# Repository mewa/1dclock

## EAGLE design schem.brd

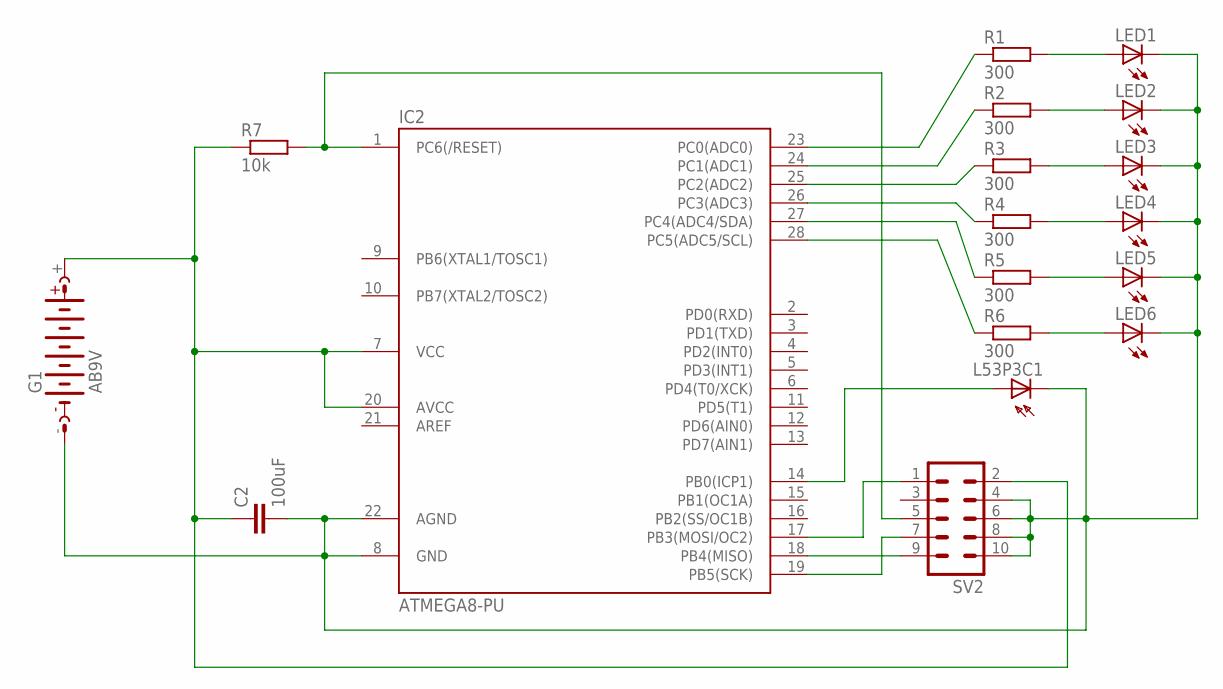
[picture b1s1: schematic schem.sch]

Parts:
C2: 100uF; C025-050X050
G1: AB9V
IC2: ATMEGA8-PU; DIL28-3
L53P3C1: BPX65
LED1, LED2, LED3, LED4, LED5, LED6: LED5MM
R1, R2, R3, R4, R5, R6: 300; 0204/5
R7: 10k; 0204/5
SV2: ML10

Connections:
unnamed: C2.2, G1.-, IC2.8 (GND), IC2.22 (AGND), L53P3C1.K (C), LED1.K (C), LED2.K (C), LED3.K (C), LED4.K (C), LED5.K (C), LED6.K (C), SV2.4, SV2.6, SV2.8, SV2.10
unnamed: IC2.23 (PC0(ADC0)), R1.1
unnamed: IC2.24 (PC1(ADC1)), R2.1
unnamed: IC2.25 (PC2(ADC2)), R3.1
unnamed: IC2.27 (PC4(ADC4/SDA)), R5.1
unnamed: IC2.28 (PC5(ADC5/SCL)), R6.1
unnamed: LED3.A, R3.2
unnamed: LED6.A, R6.2
unnamed: IC2.17 (PB3(MOSI/OC2)), SV2.1
unnamed: IC2.18 (PB4(MISO)), SV2.9
unnamed: IC2.19 (PB5(SCK)), SV2.7
unnamed: IC2.1 (PC6(/RESET)), R7.2, SV2.5
unnamed: IC2.14 (PB0(ICP1)), L53P3C1.A
unnamed: IC2.26 (PC3(ADC3)), R4.1
unnamed: LED1.A, R1.2
unnamed: LED2.A, R2.2
unnamed: LED4.A, R4.2
unnamed: LED5.A, R5.2
unnamed: C2.1, G1.+, IC2.7 (VCC), IC2.20 (AVCC), R7.1, SV2.2

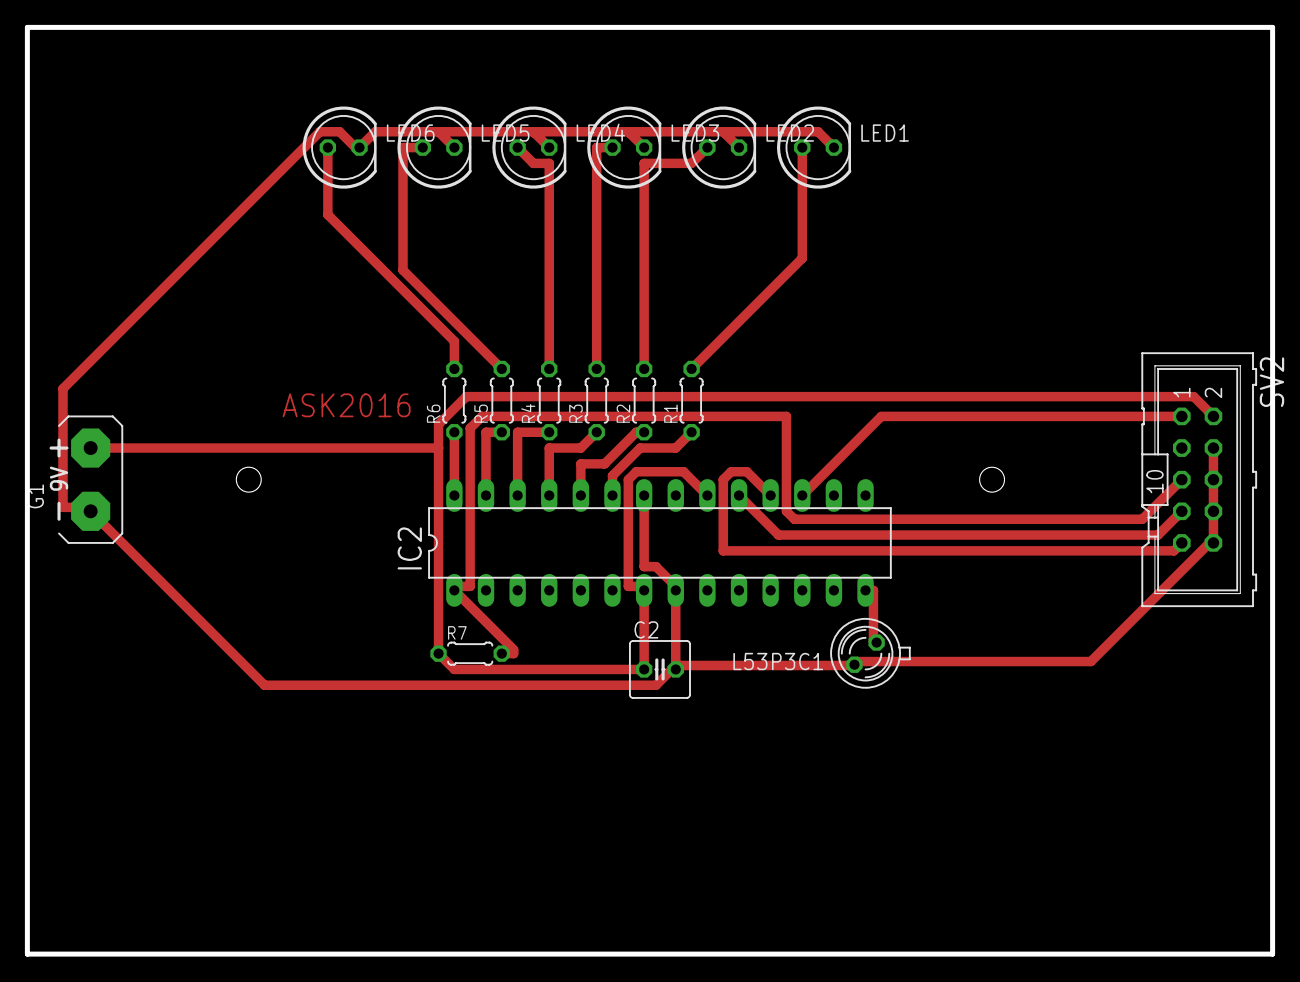
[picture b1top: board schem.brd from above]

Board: 1 copper layer, 100.0 x 74.4 mm, 18 parts (0 on the bottom side), 19 nets.
